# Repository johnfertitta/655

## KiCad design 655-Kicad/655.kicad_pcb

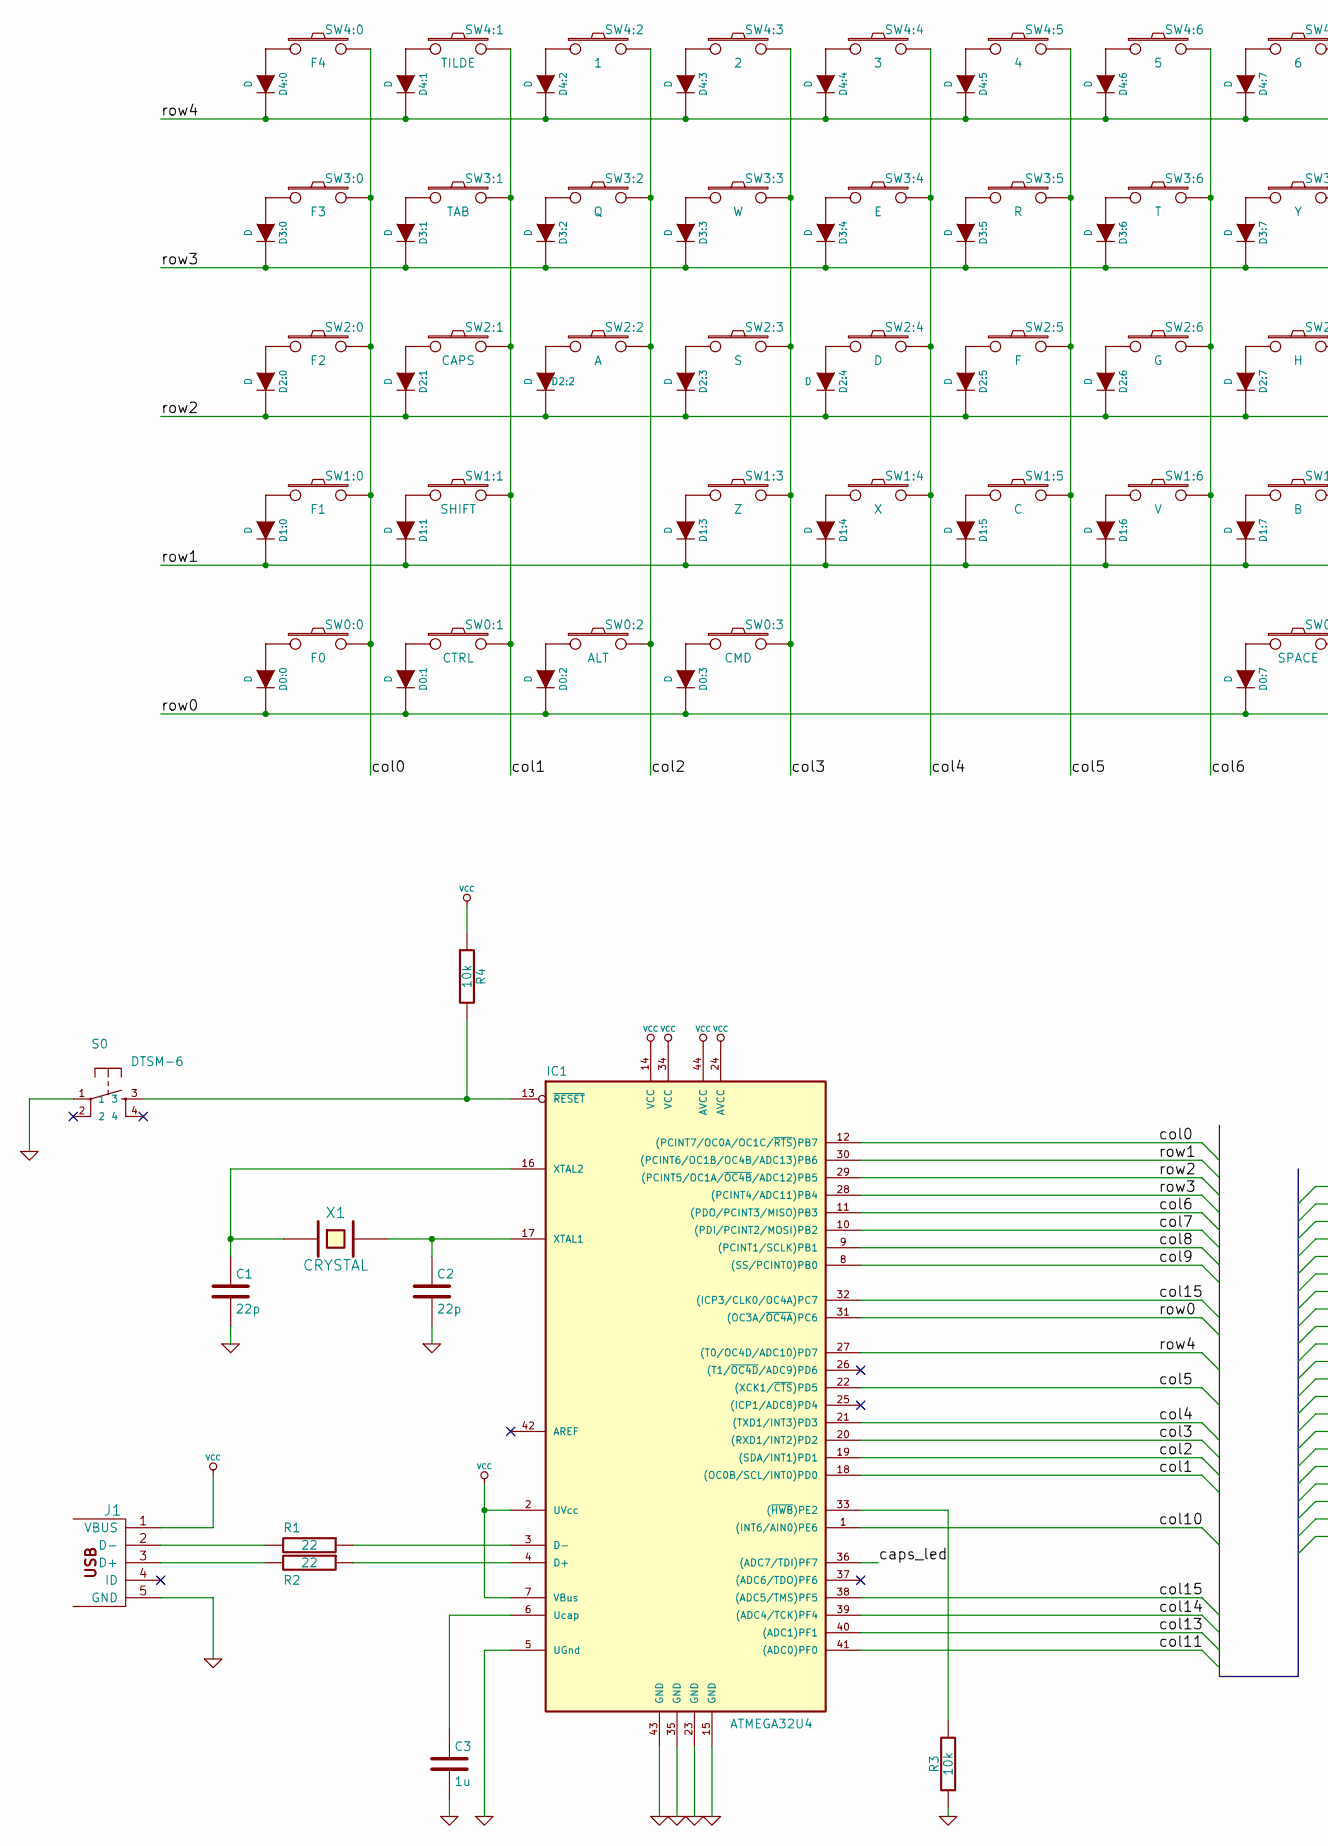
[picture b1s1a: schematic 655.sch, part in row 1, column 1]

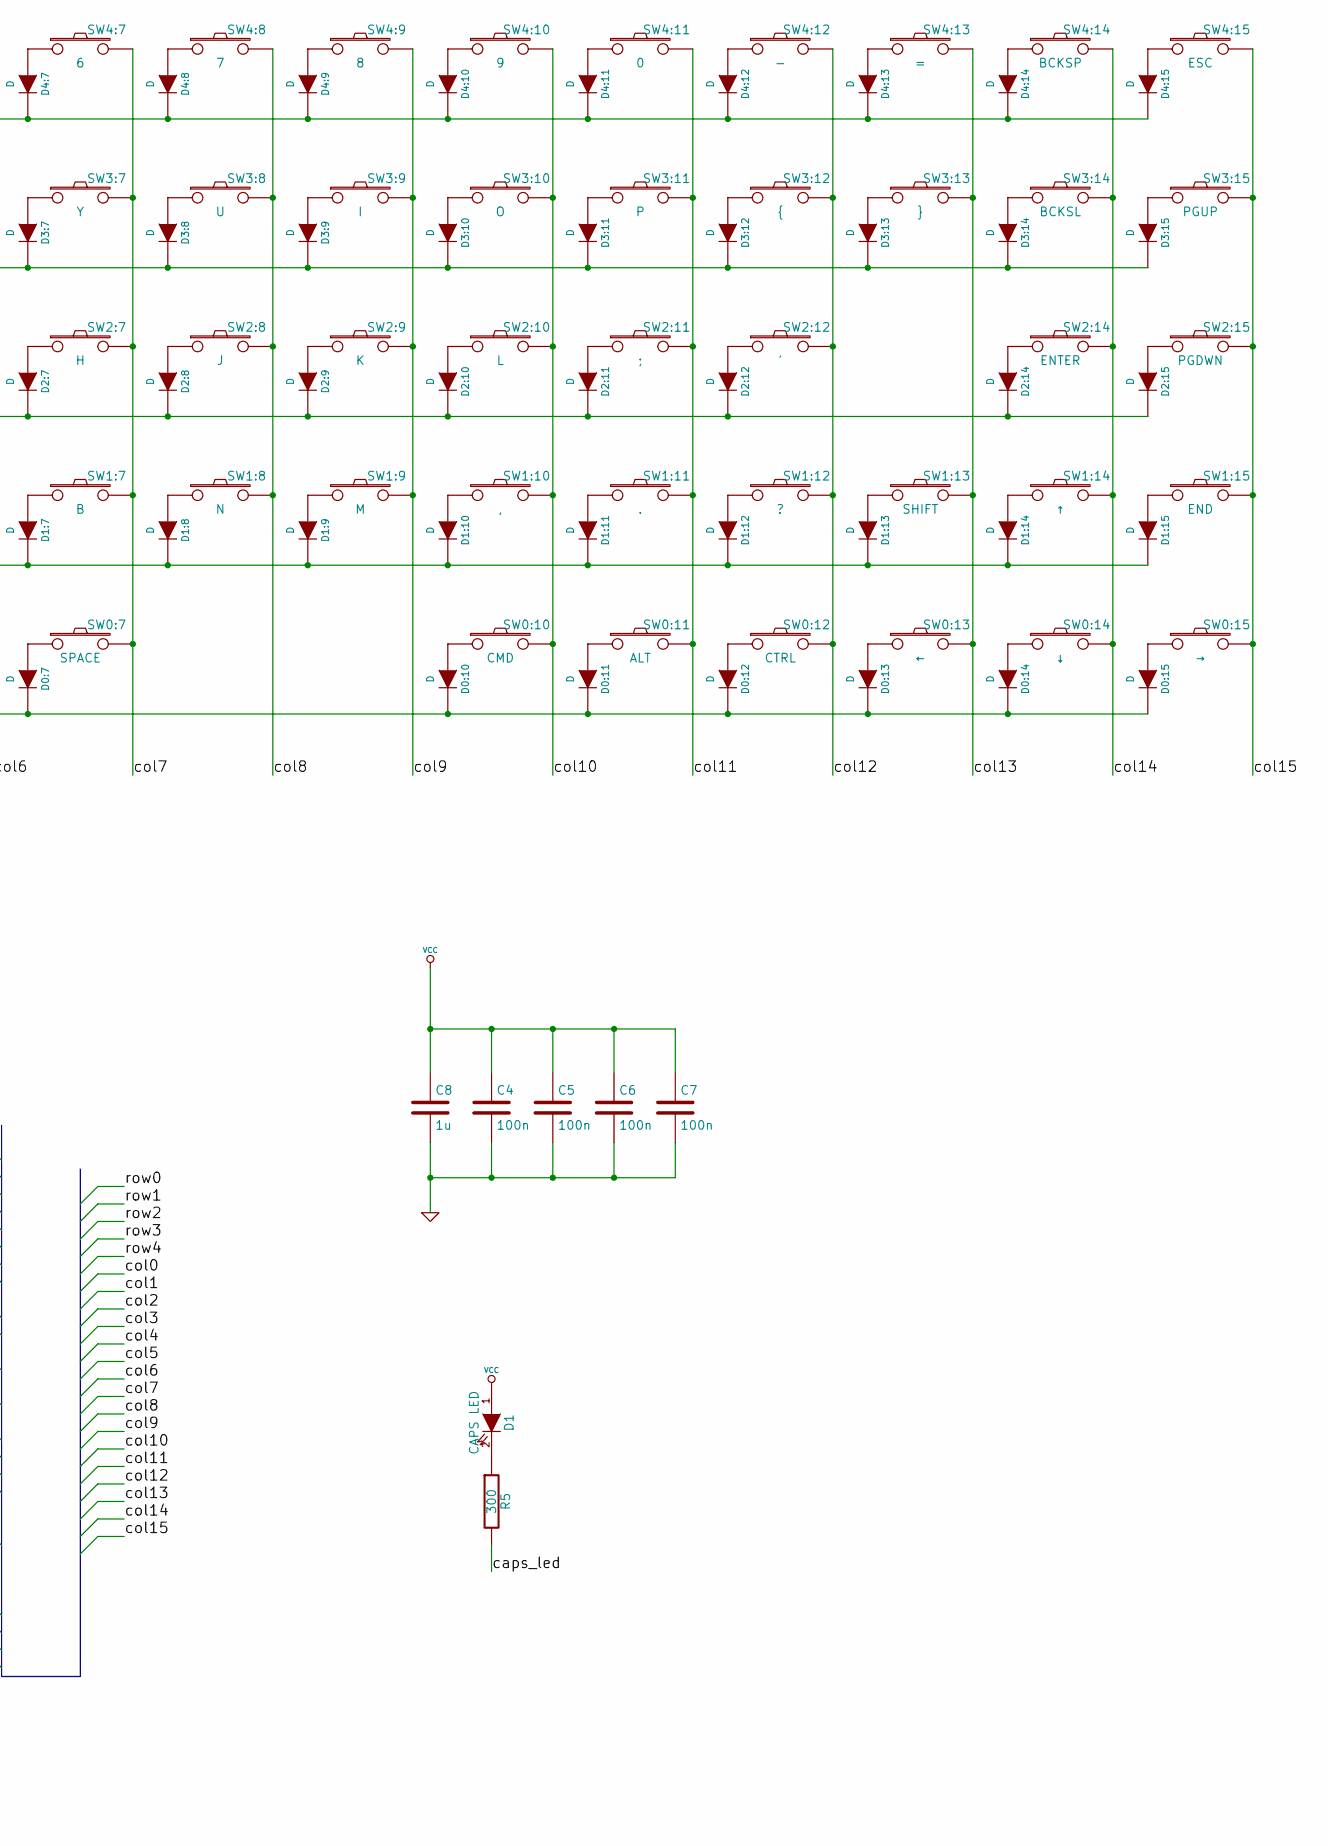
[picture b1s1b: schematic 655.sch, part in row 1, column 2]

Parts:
C1, C2: 22p; 0805C
C3, C8: 1u; 0805C
C4, C5, C6, C7: 100n; 0805C
D0:0, D0:1, D0:2, D0:3, D0:7, D0:10, D0:11, D0:12, D0:13, D0:14, D0:15, D1:0, D1:1, D1:3, D1:4, D1:5, D1:6, D1:7, D1:8, D1:9, D1:10, D1:11, D1:12, D1:13, D1:14, D1:15, D2:0, D2:1, D2:2, D2:3, D2:4, D2:5, D2:6, D2:7, D2:8, D2:9, D2:10, D2:11, D2:12, D2:14, D2:15, D3:0, D3:1, D3:2, D3:3, D3:4, D3:5, D3:6, D3:7, D3:8, D3:9, D3:10, D3:11, D3:12, D3:13, D3:14, D3:15, D4:0, D4:1, D4:2, D4:3, D4:4, D4:5, D4:6, D4:7, D4:8, D4:9, D4:10, D4:11, D4:12, D4:13, D4:14, D4:15: D; DIODE
D1: CAPS LED; MX1A-led
IC1: ATMEGA32U4; TQFP44
J1: USBMINI_B05; 67503
R1, R2: 22; 0805R
R3, R4: 10k; 0805R
R5: 300; 0805R
S0: DTSM-6; KSEM31GLFS
SW0:0: F0; MX1A
SW0:1, SW0:12: CTRL; MX1A
SW0:2, SW0:11: ALT; MX1A
SW0:3, SW0:10: CMD; MX1A
SW0:7: SPACE; MX1A
SW0:13: ←; MX1A
SW0:14: ↓; MX1A
SW0:15: →; MX1A
SW1:0: F1; MX1A
SW1:1, SW1:13: SHIFT; MX1A
SW1:3: Z; MX1A
SW1:4: X; MX1A
SW1:5: C; MX1A
SW1:6: V; MX1A
SW1:7: B; MX1A
SW1:8: N; MX1A
SW1:9: M; MX1A
SW1:10: ,; MX1A
SW1:11: .; MX1A
SW1:12: ?; MX1A
SW1:14: ↑; MX1A
SW1:15: END; MX1A
SW2:0: F2; MX1A
SW2:1: CAPS; MX1A
SW2:2: A; MX1A
SW2:3: S; MX1A
SW2:4: D; MX1A
SW2:5: F; MX1A
SW2:6: G; MX1A
SW2:7: H; MX1A
SW2:8: J; MX1A
SW2:9: K; MX1A
SW2:10: L; MX1A
SW2:11: ;; MX1A
SW2:12: '; MX1A
SW2:14: ENTER; MX1A
SW2:15: PGDWN; MX1A
SW3:0: F3; MX1A
SW3:1: TAB; MX1A
SW3:2: Q; MX1A
SW3:3: W; MX1A
SW3:4: E; MX1A
SW3:5: R; MX1A
SW3:6: T; MX1A
SW3:7: Y; MX1A
SW3:8: U; MX1A
SW3:9: I; MX1A
SW3:10: O; MX1A
SW3:11: P; MX1A
SW3:12: {; MX1A
SW3:13: }; MX1A
SW3:14: BCKSL; MX1A
SW3:15: PGUP; MX1A
SW4:0: F4; MX1A
SW4:1: TILDE; MX1A
SW4:2: 1; MX1A
SW4:3: 2; MX1A
SW4:4: 3; MX1A
SW4:5: 4; MX1A
SW4:6: 5; MX1A
SW4:7: 6; MX1A
SW4:8: 7; MX1A
SW4:9: 8; MX1A
SW4:10: 9; MX1A
SW4:11: 0; MX1A
SW4:12: -; MX1A
SW4:13: =; MX1A
SW4:14: BCKSP; MX1A
SW4:15: ESC; MX1A
X1: CRYSTAL; Crystal_HC49-U_Vertical

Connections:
/caps_led: IC1.36 ((ADC7/TDI)PF7), R5.2
/col0: IC1.12 ((PCINT7/OC0A/OC1C/~RTS~)PB7), SW0:0.2, SW1:0.2, SW2:0.2, SW3:0.2, SW4:0.2
/col1: IC1.18 ((OC0B/SCL/INT0)PD0), SW0:1.2, SW1:1.2, SW2:1.2, SW3:1.2, SW4:1.2
/col2: IC1.19 ((SDA/INT1)PD1), SW0:2.2, SW2:2.2, SW3:2.2, SW4:2.2
/col3: IC1.20 ((RXD1/INT2)PD2), SW0:3.2, SW1:3.2, SW2:3.2, SW3:3.2, SW4:3.2
/col4: IC1.21 ((TXD1/INT3)PD3), SW1:4.2, SW2:4.2, SW3:4.2, SW4:4.2
/col5: IC1.22 ((XCK1/~CTS~)PD5), SW1:5.2, SW2:5.2, SW3:5.2, SW4:5.2
/col6: IC1.11 ((PDO/PCINT3/MISO)PB3), SW1:6.2, SW2:6.2, SW3:6.2, SW4:6.2
/col7: IC1.10 ((PDI/PCINT2/MOSI)PB2), SW0:7.2, SW1:7.2, SW2:7.2, SW3:7.2, SW4:7.2
/col8: IC1.9 ((PCINT1/SCLK)PB1), SW1:8.2, SW2:8.2, SW3:8.2, SW4:8.2
/col9: IC1.8 ((SS/PCINT0)PB0), SW1:9.2, SW2:9.2, SW3:9.2, SW4:9.2
/col10: IC1.1 ((INT6/AIN0)PE6), SW0:10.2, SW1:10.2, SW2:10.2, SW3:10.2, SW4:10.2
/col11: IC1.41 ((ADC0)PF0), SW0:11.2, SW1:11.2, SW2:11.2, SW3:11.2, SW4:11.2
/col12: SW0:12.2, SW1:12.2, SW2:12.2, SW3:12.2, SW4:12.2
/col13: IC1.40 ((ADC1)PF1), SW0:13.2, SW1:13.2, SW3:13.2, SW4:13.2
/col14: IC1.39 ((ADC4/TCK)PF4), SW0:14.2, SW1:14.2, SW2:14.2, SW3:14.2, SW4:14.2
/col15: IC1.32 ((ICP3/CLK0/OC4A)PC7), IC1.38 ((ADC5/TMS)PF5), SW0:15.2, SW1:15.2, SW2:15.2, SW3:15.2, SW4:15.2
/row0: D0:0.2 (K), D0:1.2 (K), D0:2.2 (K), D0:3.2 (K), D0:7.2 (K), D0:10.2 (K), D0:11.2 (K), D0:12.2 (K), D0:13.2 (K), D0:14.2 (K), D0:15.2 (K), IC1.31 ((OC3A/~OC4A~)PC6)
/row1: D1:0.2 (K), D1:1.2 (K), D1:3.2 (K), D1:4.2 (K), D1:5.2 (K), D1:6.2 (K), D1:7.2 (K), D1:8.2 (K), D1:9.2 (K), D1:10.2 (K), D1:11.2 (K), D1:12.2 (K), D1:13.2 (K), D1:14.2 (K), D1:15.2 (K), IC1.30 ((PCINT6/OC1B/OC4B/ADC13)PB6)
/row2: D2:0.2 (K), D2:1.2 (K), D2:2.2 (K), D2:3.2 (K), D2:4.2 (K), D2:5.2 (K), D2:6.2 (K), D2:7.2 (K), D2:8.2 (K), D2:9.2 (K), D2:10.2 (K), D2:11.2 (K), D2:12.2 (K), D2:14.2 (K), D2:15.2 (K), IC1.29 ((PCINT5/OC1A/~OC4B~/ADC12)PB5)
/row3: D3:0.2 (K), D3:1.2 (K), D3:2.2 (K), D3:3.2 (K), D3:4.2 (K), D3:5.2 (K), D3:6.2 (K), D3:7.2 (K), D3:8.2 (K), D3:9.2 (K), D3:10.2 (K), D3:11.2 (K), D3:12.2 (K), D3:13.2 (K), D3:14.2 (K), D3:15.2 (K), IC1.28 ((PCINT4/ADC11)PB4)
/row4: D4:0.2 (K), D4:1.2 (K), D4:2.2 (K), D4:3.2 (K), D4:4.2 (K), D4:5.2 (K), D4:6.2 (K), D4:7.2 (K), D4:8.2 (K), D4:9.2 (K), D4:10.2 (K), D4:11.2 (K), D4:12.2 (K), D4:13.2 (K), D4:14.2 (K), D4:15.2 (K), IC1.27 ((T0/OC4D/ADC10)PD7)
GND: C1.2, C2.2, C3.2, C4.2, C5.2, C6.2, C7.2, C8.2, IC1.5 (UGnd), IC1.15 (GND), IC1.23 (GND), IC1.35 (GND), IC1.43 (GND), J1.5 (GND), R3.1, S0.1
unnamed: C1.1, IC1.16 (XTAL2), X1.1
unnamed: C2.1, IC1.17 (XTAL1), X1.2
unnamed: C3.1, IC1.6 (Ucap)
unnamed: D0:0.1 (A), SW0:0.1
unnamed: D0:1.1 (A), SW0:1.1
unnamed: D0:2.1 (A), SW0:2.1
unnamed: D0:3.1 (A), SW0:3.1
unnamed: D0:7.1 (A), SW0:7.1
unnamed: D0:10.1 (A), SW0:10.1
unnamed: D0:11.1 (A), SW0:11.1
unnamed: D0:12.1 (A), SW0:12.1
unnamed: D0:13.1 (A), SW0:13.1
unnamed: D0:14.1 (A), SW0:14.1
unnamed: D0:15.1 (A), SW0:15.1
unnamed: D1.2 (K), R5.1
unnamed: D1:0.1 (A), SW1:0.1
unnamed: D1:1.1 (A), SW1:1.1
unnamed: D1:3.1 (A), SW1:3.1
unnamed: D1:4.1 (A), SW1:4.1
unnamed: D1:5.1 (A), SW1:5.1
unnamed: D1:6.1 (A), SW1:6.1
unnamed: D1:7.1 (A), SW1:7.1
unnamed: D1:8.1 (A), SW1:8.1
unnamed: D1:9.1 (A), SW1:9.1
unnamed: D1:10.1 (A), SW1:10.1
unnamed: D1:11.1 (A), SW1:11.1
unnamed: D1:12.1 (A), SW1:12.1
unnamed: D1:13.1 (A), SW1:13.1
unnamed: D1:14.1 (A), SW1:14.1
unnamed: D1:15.1 (A), SW1:15.1
unnamed: D2:0.1 (A), SW2:0.1
unnamed: D2:1.1 (A), SW2:1.1
unnamed: D2:2.1 (A), SW2:2.1
unnamed: D2:3.1 (A), SW2:3.1
unnamed: D2:4.1 (A), SW2:4.1
unnamed: D2:5.1 (A), SW2:5.1
unnamed: D2:6.1 (A), SW2:6.1
unnamed: D2:7.1 (A), SW2:7.1
unnamed: D2:8.1 (A), SW2:8.1
unnamed: D2:9.1 (A), SW2:9.1
unnamed: D2:10.1 (A), SW2:10.1
unnamed: D2:11.1 (A), SW2:11.1
unnamed: D2:12.1 (A), SW2:12.1
unnamed: D2:14.1 (A), SW2:14.1
unnamed: D2:15.1 (A), SW2:15.1
unnamed: D3:0.1 (A), SW3:0.1
unnamed: D3:1.1 (A), SW3:1.1
unnamed: D3:2.1 (A), SW3:2.1
unnamed: D3:3.1 (A), SW3:3.1
unnamed: D3:4.1 (A), SW3:4.1
unnamed: D3:5.1 (A), SW3:5.1
unnamed: D3:6.1 (A), SW3:6.1
unnamed: D3:7.1 (A), SW3:7.1
unnamed: D3:8.1 (A), SW3:8.1
unnamed: D3:9.1 (A), SW3:9.1
unnamed: D3:10.1 (A), SW3:10.1
unnamed: D3:11.1 (A), SW3:11.1
unnamed: D3:12.1 (A), SW3:12.1
unnamed: D3:13.1 (A), SW3:13.1
unnamed: D3:14.1 (A), SW3:14.1
unnamed: D3:15.1 (A), SW3:15.1
unnamed: D4:0.1 (A), SW4:0.1
unnamed: D4:1.1 (A), SW4:1.1
unnamed: D4:2.1 (A), SW4:2.1
unnamed: D4:3.1 (A), SW4:3.1
unnamed: D4:4.1 (A), SW4:4.1
unnamed: D4:5.1 (A), SW4:5.1
unnamed: D4:6.1 (A), SW4:6.1
unnamed: D4:7.1 (A), SW4:7.1
unnamed: D4:8.1 (A), SW4:8.1
unnamed: D4:9.1 (A), SW4:9.1
unnamed: D4:10.1 (A), SW4:10.1
unnamed: D4:11.1 (A), SW4:11.1
unnamed: D4:12.1 (A), SW4:12.1
unnamed: D4:13.1 (A), SW4:13.1
unnamed: D4:14.1 (A), SW4:14.1
unnamed: D4:15.1 (A), SW4:15.1
unnamed: IC1.3 (D-), R1.1
unnamed: IC1.4 (D+), R2.1
unnamed: IC1.13 (~RESET~), R4.2, S0.3
unnamed: IC1.33 ((~HWB~)PE2), R3.2
unnamed: J1.2 (D-), R1.2
unnamed: J1.3 (D+), R2.2
VCC: C4.1, C5.1, C6.1, C7.1, C8.1, D1.1 (A), IC1.2 (UVcc), IC1.7 (VBus), IC1.14 (VCC), IC1.24 (AVCC), IC1.34 (VCC), IC1.44 (AVCC), J1.1 (VBUS), R4.1

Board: 2 copper layers, 164 parts (3 on the bottom side), 107 nets, no tracks yet.

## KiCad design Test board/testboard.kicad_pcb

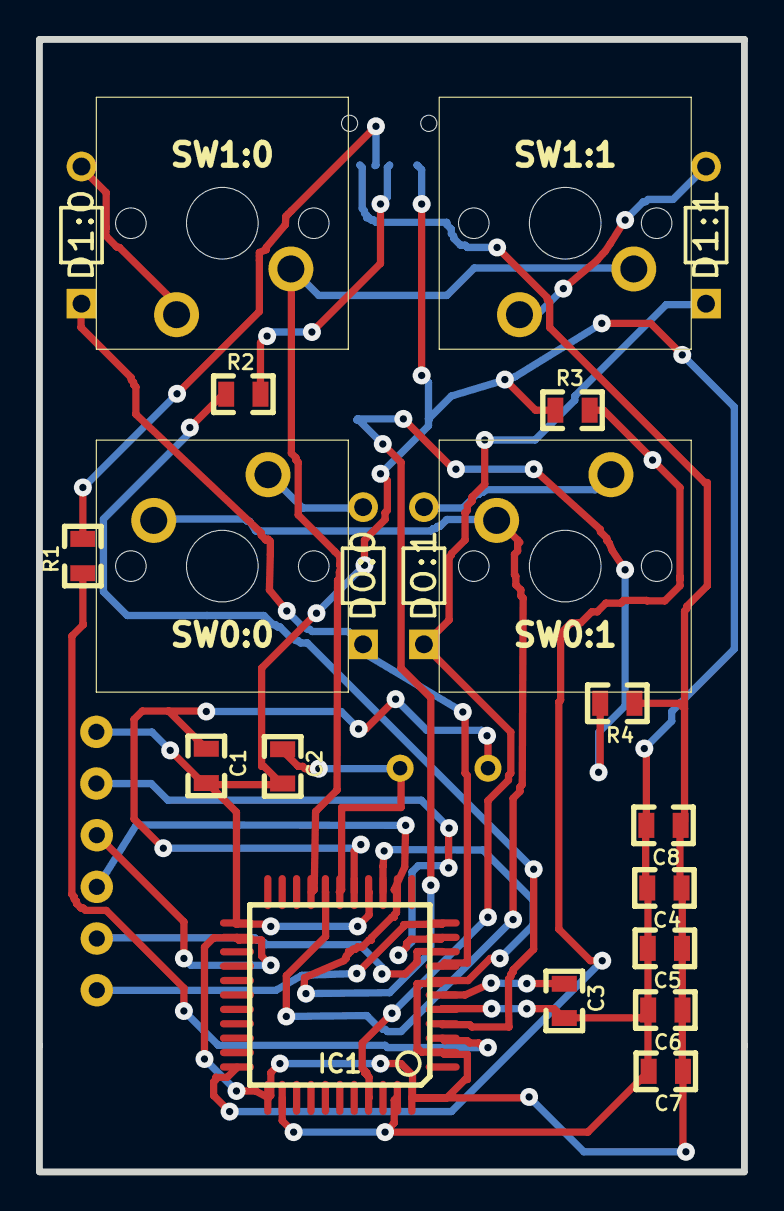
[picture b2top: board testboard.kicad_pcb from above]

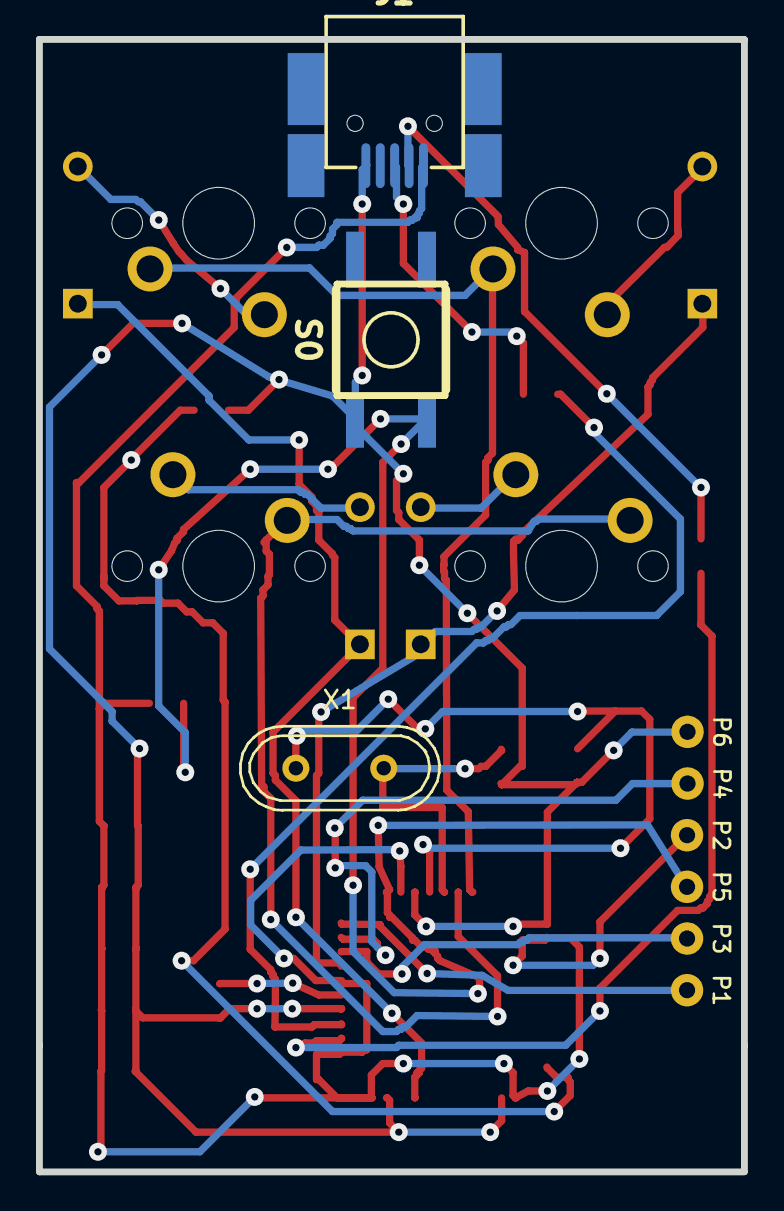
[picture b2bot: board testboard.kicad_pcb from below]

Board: 2 copper layers, 39.2 x 62.9 mm, 30 parts (9 on the bottom side), 22 nets.

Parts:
C1, C2: 22p; 0805C
C3, C8: 1u; 0805C
C4, C5, C6, C7: 100n; 0805C
D0:0, D0:1, D1:0, D1:1: D; DIODE
IC1: ATMEGA32U4; TQFP44
J1: USBMINI_B05; 67503
P1, P2, P3, P4, P5, P6: CONN_1; pad
R1, R2: 22; 0805R
R3, R4: 10k; 0805R
S0: DTSM-6; KSEM31GLFS
SW0:0: F0; MX1A
SW0:1: CTRL; MX1A
SW1:0: F1; MX1A
SW1:1: SHIFT; MX1A
X1: CRYSTAL; Crystal_HC49-U_Vertical

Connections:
/COL0: D0:0.2, D1:0.2, IC1.8
/COL1: D0:1.2, D1:1.2, IC1.41
/MISO: IC1.11, P1.1
/MOSI: IC1.10, P4.1
/RES: IC1.13, P5.1, R4.2, S0.3
/ROW0: IC1.18, SW0:0.1, SW0:1.1
/ROW1: IC1.19, SW1:0.1, SW1:1.1
/SCK: IC1.9, P3.1
GND: C1.2, C2.2, C3.2, C4.2, C5.2, C6.2, C7.2, C8.2, IC1.5, IC1.15, IC1.23, IC1.35, IC1.43, J1.5, P6.1, R3.1, S0.1
unnamed: C1.1, IC1.16, X1.1
unnamed: C2.1, IC1.17, X1.2
unnamed: C3.1, IC1.6
unnamed: D0:0.1, SW0:0.2
unnamed: D0:1.1, SW0:1.2
unnamed: D1:0.1, SW1:0.2
unnamed: D1:1.1, SW1:1.2
unnamed: IC1.3, R1.1
unnamed: IC1.4, R2.1
unnamed: IC1.33, R3.2
unnamed: J1.2, R1.2
unnamed: J1.3, R2.2
VCC: C4.1, C5.1, C6.1, C7.1, C8.1, IC1.2, IC1.7, IC1.14, IC1.24, IC1.34, IC1.44, J1.1, P2.1, R4.1

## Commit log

2016-08-23 Kicad project, layout json, case drawings
2016-08-23 update edge cuts to fit in the case
2016-08-23 I think I made gerber files?
2016-08-23 test board
2016-08-23 Test board and full board BOM files
2016-08-24 thinner cut line, moved in cut line, pdf printing files
2016-08-31 change resistor footprints to 0805R, add caps led
2016-08-31 new gerber files
2016-08-31 bon update
2016-08-31 firmware
2017-01-15 ground plane attempt
2017-07-23 fixing up matrix, re zoning, no routes
